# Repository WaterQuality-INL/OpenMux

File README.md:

# OpenMux Overview
OpenMux is an extension of the research conducted within the framework of the [OPTIRAS project](https://www.optiras.org/), particularly from the [Water Quality Group](https://inl.int/espina-research-group/) at the [International Iberian Nanotechnology Laboratory](https://inl.int/).
We aim to provide an open-source multiplexer adaptor for the [EmStat4 LR/HR potentiostat](https://www.palmsens.com/product/emstat4m/) by combining hardware design with software integration. This innovation enhances experimental efficiency and scalability for researchers and engineers at an exceptionally low cost, paving the way for applications such as multiplexed electrochemical sensing, automated assay platforms, and integrated IoT-based field monitoring systems for environmental, biomedical, or industrial electrochemical analysis.

The use of OpenMux is demonstrated in the article ["Multiplexed potentiometric sensing of nitrite in environmental waters"](https://doi.org/10.1016/j.aca.2026.345190) [1].

---

## About

This repository provides **OpenMux**, a homemade and cost-effective multiplexer adaptor for the EmStat4 OEM module from Palmsens. 
The adaptor is integrated with the potentiostat using the [**MethodScript**]([https://github.com/PalmSens](https://www.palmsens.com/methodscript/)) protocol provided by the manufacturer.

The system consists of two main modules:  

1. **Hardware Module** – the multiplexer adaptor (figure 1), whose schematics and PCB layout were developed using KiCad 7.0. Schematic, layout, and Gerber files can be found in the `Hardware/` folder (see [schematic.pdf](Hardware/schematic.pdf) and [layout.pdf](Hardware/layout.pdf) for pictures).  
2. **Graphical User Interface (GUI)** – a graphical user interface (figure 2) to control the adaptor, implemented in Python 3.8. The GUI is located in the `Application/`  folder.

<div align="center">
  
  <p><em>Figure 1: OpenMux adaptor for EmStat4</em></p>
</div>

<div align="center">
  
  <p><em>Figure 2: OpenMux GUI</em></p>
</div>

The application of OpenMux for electrochemical methods is described in the scientific literature [2].

## Who is this for?

- Electrochemists who want a cheap and modular, open platform for integrating sensors and data backends for:
   - Environmental or industrial monitoring applications
   - Scaling up sensor optimisation and/or preparation in the lab
  
---

## Costs

The approximate cost of the electronic components (excluding the PCB) is around **€40**. Key components include:

| Quantity | Component | Price | Link |
|----------|-----------|-------|------|
| 3x       | ADG1408YRUZ Multiplexer | €10 | [Digi-Key](https://www.digikey.pt/en/products/detail/analog-devices-inc/ADG1408YRUZ/1206709?msockid=3b4fa386dcfd658b16a1b206dd9a641a) |
| 3x       | Phoenix Terminal Block 8-pos | €1.60 | [Digi-Key](https://www.digikey.pt/en/products/detail/phoenix-contact/1984675/950853) |
| 3x       | Male Pin Header 12-pos | €0.14 | [Digi-Key](https://www.digikey.pt/en/products/detail/adam-tech/PH1-12-UA/9830395) |
| 3x       | Female Pin Header 12-pos | €0.49 | [Digi-Key](https://www.digikey.pt/en/products/detail/w%C3%BCrth-elektronik/61301211821/16608531) |

---

## Getting Started

1) Clone or download the repository 
```bash
git clone https://github.com/WaterQuality-INL/OpenMux.git
cd OpenMux
```

2) Hardware and production
- Gerber files for production: `Hardware/production/Mux_Module.zip`
- Schematics and PCB: in `Hardware/` (KiCad 7.x)
- Fabricate the PCB (JLCPCB, PCBWay, etc.), order components, and assemble.

3) Software requirements
- Python 3.8 or newer (3.8–3.11 recommended)
- OS: Windows, Linux, or macOS (GUI tested on Windows; Linux/macOS supported)
- The Application uses `MethodScript-firmware/` and `Icons/` folders; these must be present when running the packaged executable (see Packaging below).

4) Run the GUI (development)

Windows (cmd / PowerShell)
```bash
cd Application
python -m venv venv
venv\Scripts\activate.bat    # PowerShell: venv\Scripts\Activate.ps1
pip install -r requirements.txt
python EL_MUX.py
```

Linux / macOS
```bash
cd Application
python3 -m venv venv
source venv/bin/activate
pip install -r requirements.txt
python3 EL_MUX.py
```

5) OPTIONAL: Packaging (creating an executable)

Alternatively, an executable file can also be created, allowing this application to run in computers where python is not installed.
```bash
cd Application
venv\Scripts\activate.bat
pyinstaller -w -p "venv\Lib\site-packages" -i Icons/group-30_116053.ico --onefile EL_MUX.py
```

Notes:
- The produced executable still depends on the folders `MethodScript-firmware/` and `Icons/`. Place `EL_MUX.exe` into `Application/` alongside those folders before running.
- After verifying the executable works, you can remove the `build/` and `dist/` directories.

---

## Troubleshooting

- If the GUI cannot find the EmStat4 device, verify the USB/serial connection and port name.
- Ensure the virtual environment is activated and dependencies installed.
- For packaging issues, build the executable on the target OS (pyinstaller builds are OS-specific).

---

## License

- Software (Application/) is licensed under the MIT License.  
- <p> Hardware (Hardware/) is licensed under <a href=https://creativecommons.org/licenses/by/4.0/> CC BY 4.0 </a>    </p>

---

## Contributors
- Samuel Silva*

Supervision:
- Álvaro Geraldes**

Contacts:
- Samuel Silva, samuel.silva@inl.int
- Álvaro Geraldes, alvaro.geraldes@inl.int

*Water Quality Group, **Systems Engineering Group, International Iberian Nanotechnology Laboratory (INL)

---

## Acknowledgement
To PalmSens for MethodScript

This work is an extension of the research project funded by EEA (European Economic Area) Grants Portugal through the funded project PT-INN-0076—OPTIRAS.

---

## References
[1] Renato L. Gil, Samuel Silva, Marília B. Santos, Álvaro Geraldes, Begoña Espiña, Raquel B. Queirós. Multiplexed potentiometric sensing of nitrite in environmental waters. Analytica Chimica Acta 2026, https://doi.org/10.1016/j.aca.2026.345190

[2] Olesia Dudik, Renato L. Gil, Raquel B. Queirós. Critical assessment of different ion-to-electron transducers in modified screen-printed electrodes for potentiometric lithium sensing. Microchemical Journal 2025, 215, 114195, https://doi.org/10.1016/j.microc.2025.114195

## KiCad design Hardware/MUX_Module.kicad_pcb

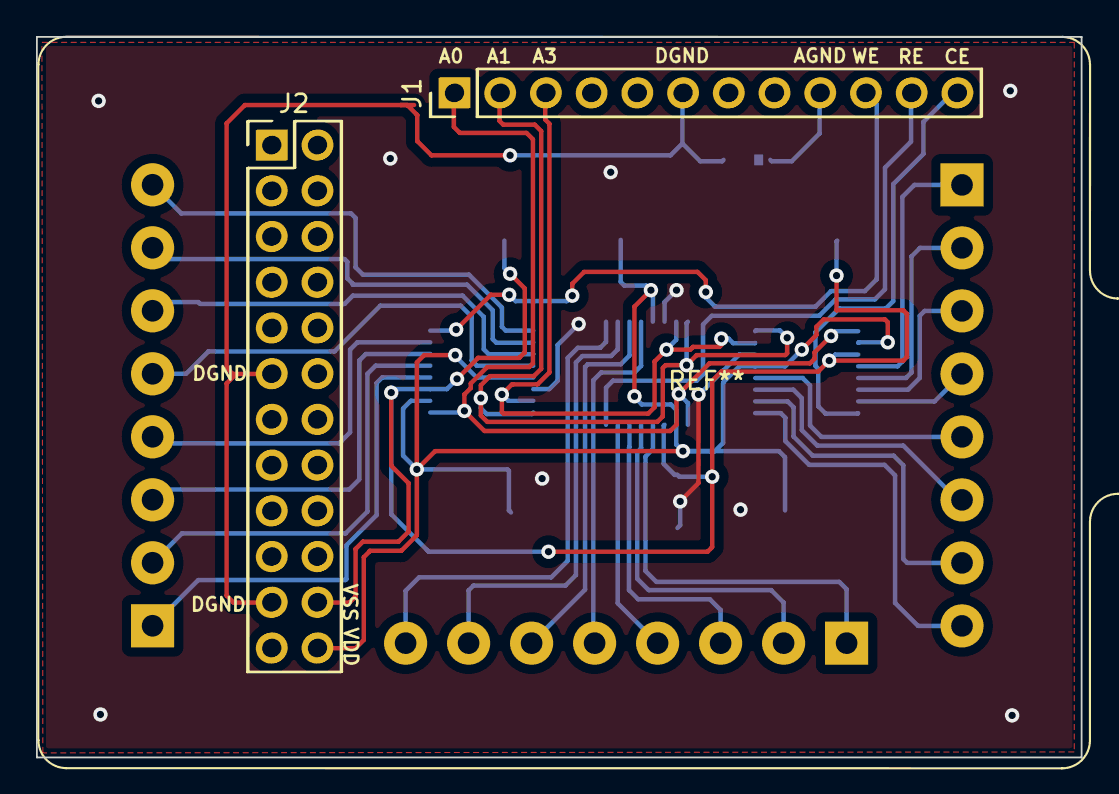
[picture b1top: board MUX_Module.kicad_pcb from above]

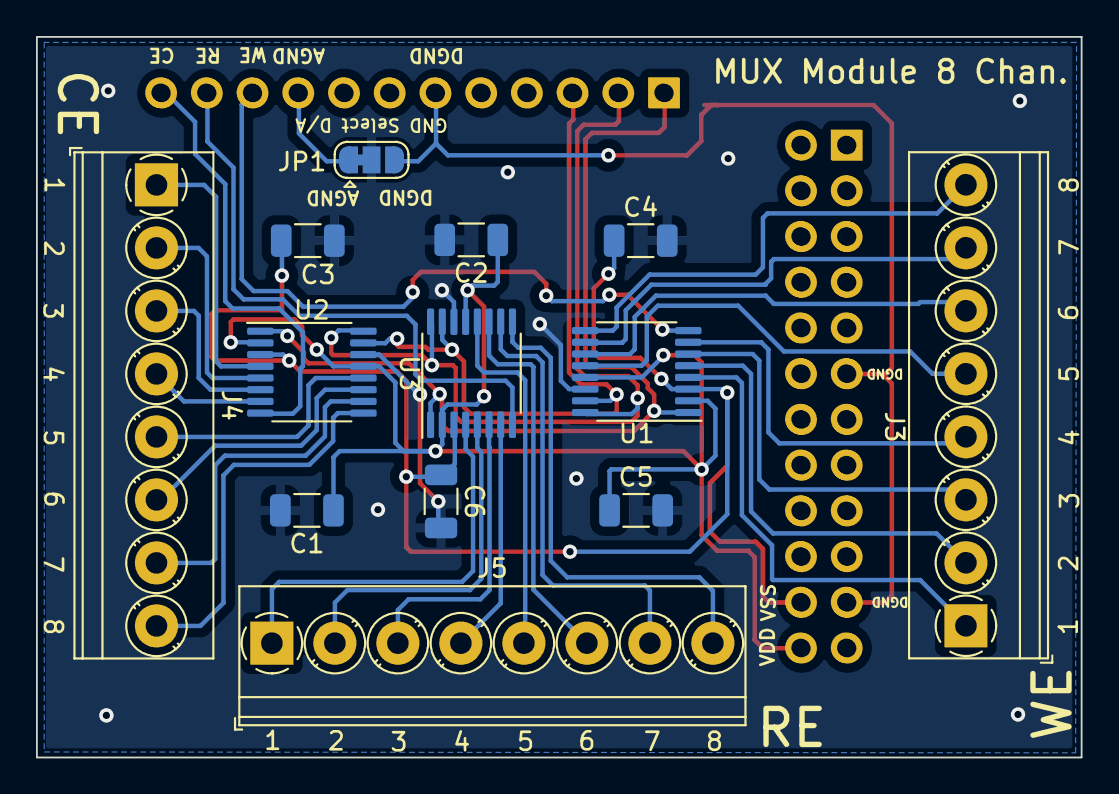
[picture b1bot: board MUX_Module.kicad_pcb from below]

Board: 2 copper layers, 58.0 x 40.0 mm, 15 parts (13 on the bottom side), 35 nets.

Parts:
C1, C2, C3, C4, C5, C6: 0.1uF; C_1206_3216Metric
J1: CON1_EmStat4; PinHeader_1x12_P2.54mm_Vertical
J2: CON2_3_EmStat4; PinHeader_2x12_P2.54mm_Vertical
J3, J4, J5: Screw_Terminal_01x08; TerminalBlock_Phoenix_PT-1,5-8-3.5-H_1x08_P3.50mm_Horizontal
JP1: SolderJumper_3_Bridged123; SolderJumper-3_P1.3mm_Bridged12_RoundedPad1.0x1.5mm
U1, U2, U3: ADG1408YRUZ; TSSOP-16_4.4x5mm_P0.65mm

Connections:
AGND: J1.9, JP1.1 (A)
CE_Pin: J1.12, U2.8 (D)
CON1_1/D3 -> A0: J1.1, U1.1 (A0), U2.1 (A0), U3.1 (A0)
CON1_2/D2 -> A1: J1.2, U1.16 (A1), U2.16 (A1), U3.16 (A1)
CON1_3/D3 -> A3: J1.3, U1.15 (A2), U2.15 (A2), U3.15 (A2)
DGND: J1.6, JP1.3 (B)
GND: C1.2, C2.2, C3.2, C4.2, C5.2, C6.2, JP1.2 (C), U1.14 (GND), U2.14 (GND), U3.14 (GND)
unnamed: J3.1, U1.4 (S1)
unnamed: J3.2, U1.5 (S2)
unnamed: J3.3, U1.6 (S3)
unnamed: J3.4, U1.7 (S4)
unnamed: J3.5, U1.12 (S5)
unnamed: J3.6, U1.11 (S6)
unnamed: J3.7, U1.10 (S7)
unnamed: J3.8, U1.9 (S8)
unnamed: J4.1, U2.4 (S1)
unnamed: J4.2, U2.5 (S2)
unnamed: J4.3, U2.6 (S3)
unnamed: J4.4, U2.7 (S4)
unnamed: J4.5, U2.12 (S5)
unnamed: J4.6, U2.11 (S6)
unnamed: J4.7, U2.10 (S7)
unnamed: J4.8, U2.9 (S8)
unnamed: J5.1, U3.4 (S1)
unnamed: J5.2, U3.5 (S2)
unnamed: J5.3, U3.6 (S3)
unnamed: J5.4, U3.7 (S4)
unnamed: J5.5, U3.12 (S5)
unnamed: J5.6, U3.11 (S6)
unnamed: J5.7, U3.10 (S7)
unnamed: J5.8, U3.9 (S8)
RE_Pin: J1.11, U3.8 (D)
VDD: C1.1, C2.1, C5.1, U1.2 (EN), U1.13 (VDD), U2.2 (EN), U2.13 (VDD), U3.2 (EN), U3.13 (VDD)
VSS: C3.1, C4.1, C6.1, U1.3 (VSS), U2.3 (VSS), U3.3 (VSS)
WE_Pin: J1.10, U1.8 (D)

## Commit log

2025-09-12 adding readme
2025-09-12 Adding hardware
2025-09-12 Add licenses
2025-11-17 Enhance README with troubleshooting section
    Added troubleshooting tips for GUI and packaging issues.
2025-11-17 Revise README structure and content
    Updated README to improve clarity and organization, including section headings and additional information.
2025-11-17 Refactor README for better clarity and formatting
    Removed unnecessary line breaks and improved formatting in the README.
2025-11-18 Adding pdf files with schematics and layout
2025-11-18 Clarify hardware module documentation in README
    Updated README to clarify file locations and add references to schematic and layout images.
2025-11-18 Fix links to schematic and layout PDFs in README
    Updated links in README for schematic and layout files.
2025-11-18 Fix markdown links in README.md
2025-11-18 Fix typos in README.md for consistency
2025-11-18 Update LICENSE
2025-11-18 Enhance hardware license section in README
    Updated hardware license information with a link and image.
2025-11-18 Fix wording in acknowledgement section
2026-02-02 Add demonstration article link to README
    Added a demonstration article for OpenMux usage.
2026-02-02 Revise article references in README.md
    Updated reference numbers for articles demonstrating OpenMux usage and application in electrochemical methods.
2026-02-02 Revise readme
